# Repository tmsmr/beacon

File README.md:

# beacon
*Work in progress*

## Components
### Device
[KiCAD Project](./beacon.kicad)

</br>
**Development PCB*

### Firmware
[Pico-SDK project](./firmware)

## Attribution
### PCB
RP2354A-specific design is based on https://datasheets.raspberrypi.com/rp2350/Minimal-KiCAD.zip

### USB HID
The USB HID implementation is based on various sources:
- https://github.com/hathach/tinyusb
- https://github.com/raspberrypi/pico-examples
- https://github.com/bluekeyes/pico-12vrgb-hid-controller

### SK6812
https://github.com/PDBeal/pico-sk6812

### Icon
<a href="https://www.flaticon.com/free-icons/alarm" title="alarm icons">Alarm icons created by Magnific - Flaticon</a>

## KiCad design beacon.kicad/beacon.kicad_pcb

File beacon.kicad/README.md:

# beacon.kicad

- Design rules imported from https://github.com/AislerHQ/aisler-support/tree/master/kicad/aisler-2-layer-simple-drc

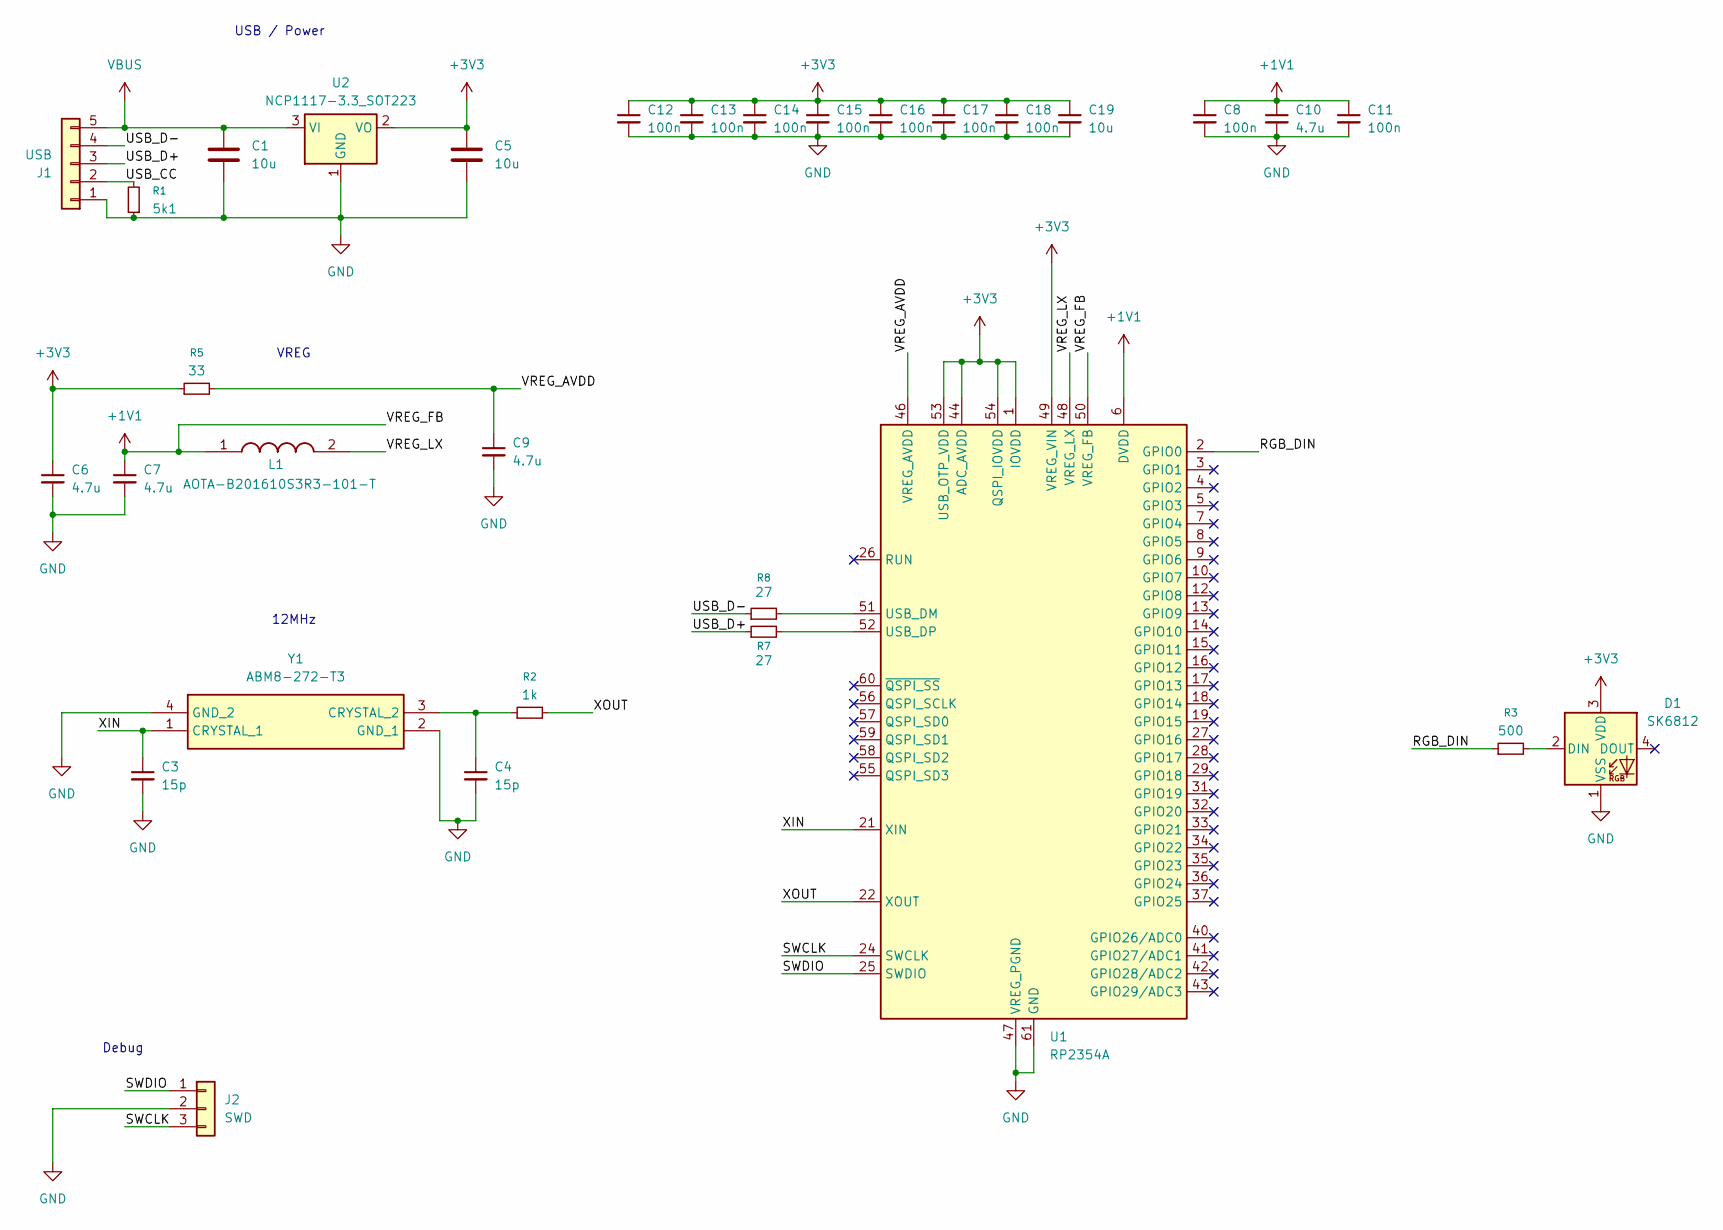
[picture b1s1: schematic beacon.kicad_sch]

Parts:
C1, C5, C19: 10u; C_0805_2012Metric
C3, C4: 15p; C_0805_2012Metric
C6, C7: 4.7u; C_0402_1005Metric_small_pads
C8, C11, C12, C13, C14, C15, C16, C17, C18: 100n; C_0805_2012Metric
C9: 4.7u; C_0402_1005Metric
C10: 4.7u; C_0805_2012Metric
D1: SK6812; LED_SK6812_PLCC4_5.0x5.0mm_P3.2mm
J1: USB; PinHeader_1x05_P1.27mm_Horizontal
J2: SWD; PinHeader_1x03_P1.27mm_Horizontal
L1: AOTA-B201610S3R3-101-T; AOTAB201610S3R3101T; Manufacturer_Part_Number AOTA-B201610S3R3-101-T; Mouser Part Number 815-AB201610S3R3101T
R1: 5k1; R_0402_1005Metric
R2: 1k; R_0805_2012Metric
R3: 500; R_0805_2012Metric
R5: 33; R_0402_1005Metric
R7, R8: 27; R_0402_1005Metric
U1: RP2354A; RP2354A-QFN-60-1EP_7x7_P0.4mm_EP3.4x3.4mm_ThermalVias
U2: NCP1117-3.3_SOT223; SOT-223-3_TabPin2
Y1: ABM8-272-T3; ABM8272T3; Manufacturer_Part_Number ABM8-272-T3; Mouser Part Number 815-ABM8-272-T3

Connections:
+1V1: C7.1, C8.1, C10.1, C11.1, L1.1, U1.6 (DVDD), U1.23 (DVDD), U1.39 (DVDD), U1.50 (VREG_FB)
+3V3: C5.1, C6.1, C12.1, C13.1, C14.1, C15.1, C16.1, C17.1, C18.1, C19.1, D1.3 (VDD), R5.1, U1.1 (IOVDD), U1.11 (IOVDD), U1.20 (IOVDD), U1.30 (IOVDD), U1.38 (IOVDD), U1.44 (ADC_AVDD), U1.45 (IOVDD), U1.49 (VREG_VIN), U1.53 (USB_OTP_VDD), U1.54 (QSPI_IOVDD), U2.2 (VO)
/RGB_DIN: R3.1, U1.2 (GPIO0)
/SWCLK: J2.3, U1.24 (SWCLK)
/SWDIO: J2.1, U1.25 (SWDIO)
/USB_CC: J1.2, R1.2
/USB_D+: J1.3, R7.1
/USB_D-: J1.4, R8.1
/VREG_AVDD: C9.1, R5.2, U1.46 (VREG_AVDD)
/VREG_LX: L1.2, U1.48 (VREG_LX)
/XIN: C3.1, U1.21 (XIN), Y1.1 (CRYSTAL_1)
/XOUT: R2.2, U1.22 (XOUT)
GND: C1.2, C3.2, C4.2, C5.2, C6.2, C7.2, C8.2, C9.2, C10.2, C11.2, C12.2, C13.2, C14.2, C15.2, C16.2, C17.2, C18.2, C19.2, D1.1 (VSS), J1.1, J2.2, R1.1, U1.47 (VREG_PGND), U1.61 (GND), U2.1 (GND), Y1.2 (GND_1), Y1.4 (GND_2)
unnamed: D1.2 (DIN), R3.2
unnamed: R8.2, U1.51 (USB_DM)
unnamed: R7.2, U1.52 (USB_DP)
unnamed: C4.1, R2.1, Y1.3 (CRYSTAL_2)
VBUS: C1.1, J1.5, U2.3 (VI)

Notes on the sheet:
Debug
USB / Power
VREG
12MHz

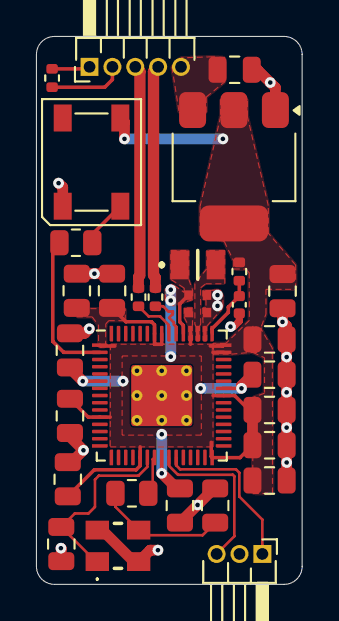
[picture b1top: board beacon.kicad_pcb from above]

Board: 2 copper layers, 14.8 x 30.4 mm, 31 parts (0 on the bottom side), 18 nets.
